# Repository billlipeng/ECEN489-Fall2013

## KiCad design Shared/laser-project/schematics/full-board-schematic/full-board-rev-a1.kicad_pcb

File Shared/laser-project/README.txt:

what implemented:
 Scene set up 
 Planes drawn
 Spheres drawn
 Ambient lighting 
 Diffuse lighting 
 Specular lighting 
 Numbers of Objects, lights, etc. meet requirements

what NOT implement:
 Shadows 
 Reflection (press key '1' to display , press key '2' to restore)

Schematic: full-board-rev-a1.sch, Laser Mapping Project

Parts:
C1, C2, C3, C4, C5, C6, C7, C8, C9, C10, C11, C12, C13: SMCAP; SM1210
CON1: ENCODER-10MIL-HEADER; encoder-10mil-header
CON2: JTAG-10MIL-HDR; JTAG-10mil-hdr
LD1: OPV332; LED-5MM
R1, R2, R3, R4, R5, R6, R7, R8, R9, R10, R11, R12, R13: SMRES; SM1210
T1, T2: BSS138; SOT23
T3: OP598C; LED-5MM
U1: TEENSYPP2
U2, U5: MCP1825; SOT-223-5pin
U3: DS1077; SO8N
U4: AD8302
U6: 6DOF; PIN_ARRAY-6X1
U7: TI-OPA2356

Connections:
/ad8302_inpa: C3.2, U4.2 (INPA)
/ad8302_inpb: C1.2, U4.6 (INPB)
/ad8302_mag: U1.40 (PF0), U4.12 (MSET), U4.13 (VMAG)
/ad8302_ofsa: C4.2, U4.3 (OFSA)
/ad8302_ofsb: C2.2, U4.5 (OFSB)
/ad8302_phs: U1.39 (PF1), U4.9 (VPHS), U4.10 (PSET)
/ad8302_vpos: C9.2, R11.1, U4.4 (VPOS)
/ad8302_vref: U1.41 (AREF), U4.11 (VREF)
/encoder-interface-0: CON1.3, U1.53 (PE4)
/encoder-interface-1: CON1.4, U1.54 (PE5)
/encoder-interface-2: CON1.5, U1.43 (PE6)
/encoder-interface-3: CON1.6, U1.44 (PE7)
/jtag_tck: CON2.1, U1.36 (PF4)
/jtag_tdi: CON2.4, U1.33 (PF7)
/jtag_tdo: CON2.3, U1.34 (PF6)
/jtag_tms: CON2.2, U1.35 (PF5)
/laser_drive_sig: R7.2, U7.1, U7.2
/mod_sig_1: C3.1, R5.2, U3.1 (OUT1), U7.3
/osc_ctrl0: U1.13 (PC0), U3.5 (CTRL0)
/osc_ctrl1: U1.14 (PC1), U3.6 (CTRL1)
/regulator_3.3V: C7.2, CON1.2, R1.2, R4.2, R9.2, T1.1 (G), T2.1 (G), U2.4 (VOUT), U6.6 (3.3V)
/regulator_5V: C5.2, C8.2, C13.2, CON1.1, R3.2, R6.2, R11.2, R12.2, T3.1 (C), U1.21 (VCC), U3.3 (VCC), U5.4 (VOUT), U7.8
/return_sig: C1.1, R2.2, R8.2, T3.2 (E)
/teensy_5V: C6.2, C10.2, U1.52 (VCC), U2.1 (SHDN), U2.2 (VIN), U5.1 (SHDN), U5.2 (VIN)
/twi_scl_3.3V: R1.1, T1.2 (S), U6.3 (SCL)
/twi_scl_5V: R3.1, T1.3 (D), U1.3 (PD0), U3.8 (SCL)
/twi_sda_3.3V: R4.1, T2.2 (S), U6.4 (SDA)
/twi_sda_5V: R6.1, T2.3 (D), U1.4 (PD1), U3.7 (SDA)
GND: C2.1, C4.1, C5.1, C6.1, C7.1, C8.1, C9.1, C10.1, C11.1, C12.1, C13.1, CON1.7, LD1.2, R2.1, R5.1, R8.1, R10.1, R13.1, U1.1 (GND), U1.22 (GND), U1.42 (GND), U2.3 (GND), U2.6 (GNDPAD), U3.4 (GND), U4.1 (COMM), U4.7 (COMM), U5.3 (GND), U5.6 (GNDPAD), U6.5 (GND), U7.4
unnamed: LD1.1, R7.1
unnamed: C12.2, U4.14 (MFLT)
unnamed: C11.2, U4.8 (PFLT)
unnamed: R12.1, R13.2, U5.5 (ADJ)
unnamed: R9.1, R10.2, U2.5 (ADJ)

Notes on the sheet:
C1,C2 May be left open.

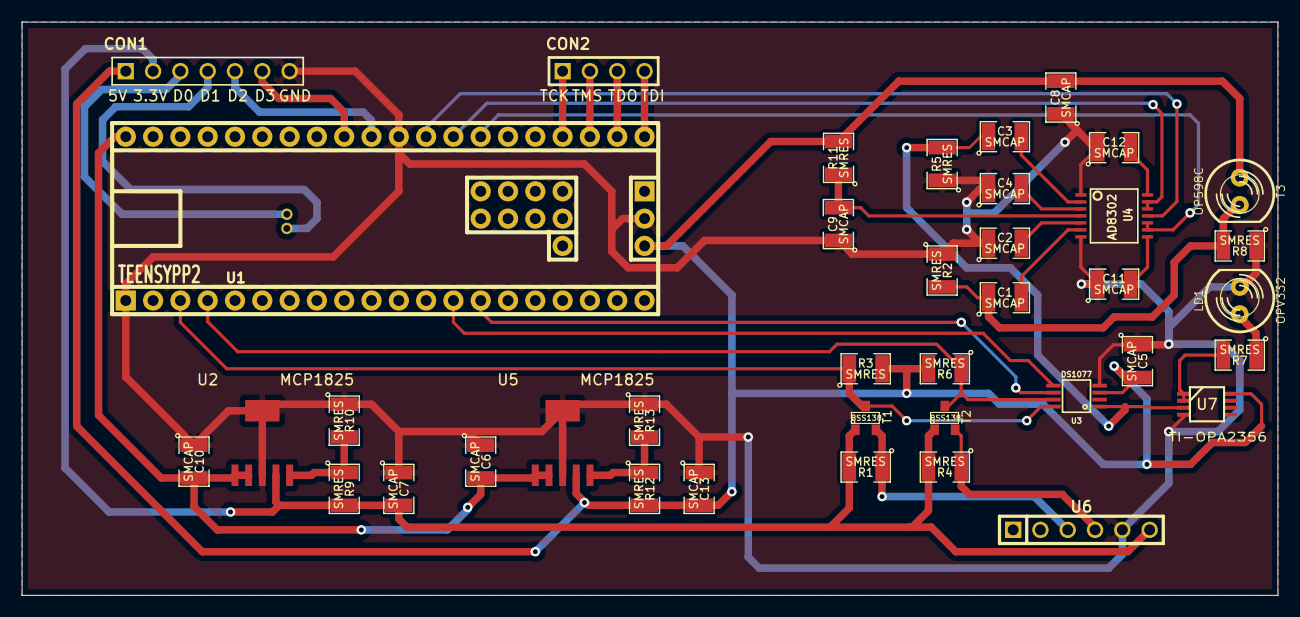
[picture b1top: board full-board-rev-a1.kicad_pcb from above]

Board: 2 copper layers, 116.8 x 53.3 mm, 39 parts (0 on the bottom side), 34 nets.

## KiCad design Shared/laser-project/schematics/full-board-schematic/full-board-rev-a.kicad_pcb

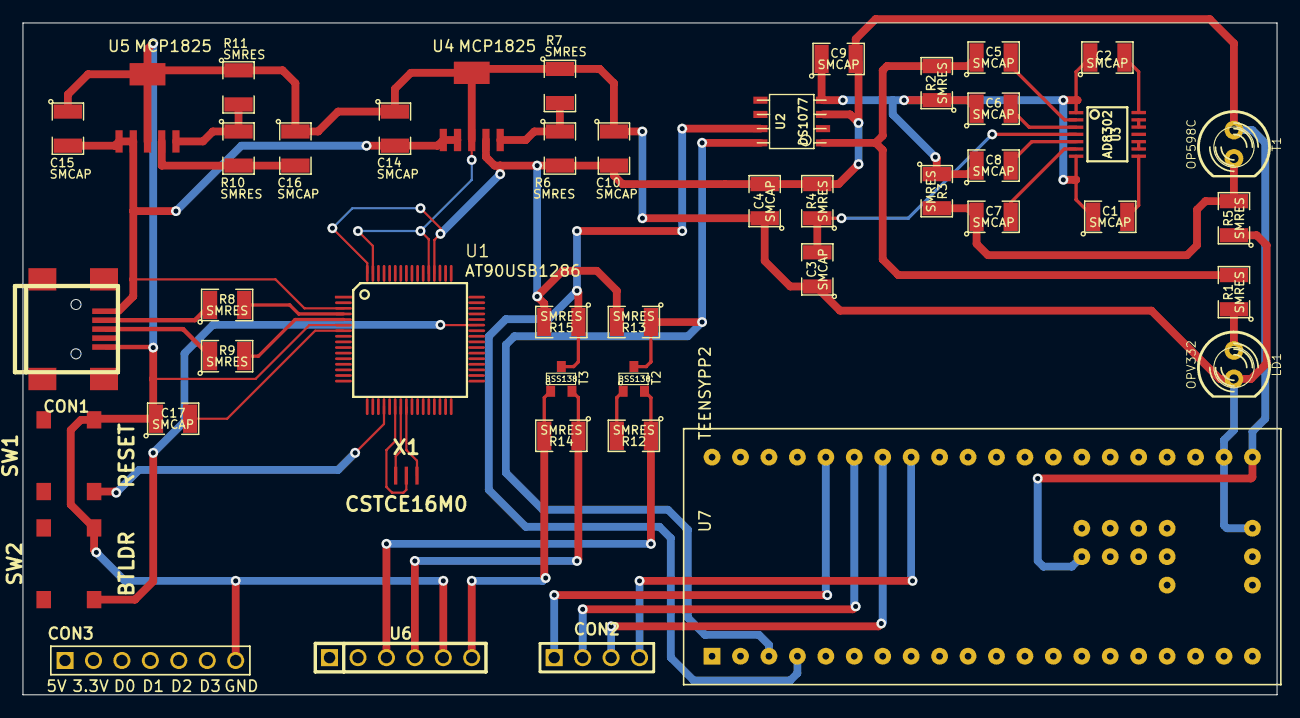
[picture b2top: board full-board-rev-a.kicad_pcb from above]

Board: 2 copper layers, 112.0 x 60.0 mm, 46 parts (0 on the bottom side), 42 nets.

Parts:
C1, C2, C3, C4, C5, C6, C7, C8, C9, C10, C14, C15, C16, C17: SMCAP; SM1210
CON1: USB-MINI-B; usb-mini-b
CON2: JTAG-10MIL-HDR; JTAG-10mil-hdr
CON3: ENCODER-10MIL-HEADER; encoder-10mil-header
LD1: OPV332; LED-5MM
R1, R2, R3, R4, R5, R6, R7, R8, R9, R10, R11, R12, R13, R14, R15: SMRES; SM1210
SW1: RESET; SW
SW2: BTLDR; SW
T1: OP598C; LED-5MM
T2, T3: BSS138; SOT23
U1: AT90USB1286; TQFP_64
U2: DS1077; so-8
U3: AD8302; TSSOP14
U4, U5: MCP1825; SOT-223-5pin
U6: 6DOF; PIN_ARRAY-6X1
U7: TEENSYPP2; Teensy++2.0
X1: CSTCE16M0; 16MHzRES

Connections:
/ad8302_inpa: C5.2, U3.2
/ad8302_inpb: C7.2, U3.6
/ad8302_mag: U1.61, U3.12, U3.13, U7.40
/ad8302_ofsa: C6.2, U3.3
/ad8302_ofsb: C8.2, U3.5
/ad8302_phs: U1.60, U3.9, U3.10, U7.39
/ad8302_vpos: C3.2, R4.1, U3.4
/ad8302_vref: U1.62, U3.11, U7.41
/encoder-interface-0: CON3.3, U1.18
/encoder-interface-1: CON3.4, U1.19
/encoder-interface-2: CON3.5, U1.1, U7.43
/encoder-interface-3: CON3.6, U1.2, U7.44
/hwb_sig: SW2.2, U1.43
/jtag_tck: CON2.1, U1.57, U7.36
/jtag_tdi: CON2.4, U1.54, U7.33
/jtag_tdo: CON2.3, U1.55, U7.34
/jtag_tms: CON2.2, U1.56, U7.35
/mod_sig_1: C5.1, R1.2, R2.2, U2.1
/osc_ctrl0: U1.35, U2.5, U7.13
/osc_ctrl1: U1.36, U2.6, U7.14
/regulator_3.3V: C16.2, CON3.2, R10.2, R12.2, R14.2, T2.1, T3.1, U5.4, U6.6
/regulator_5V: C4.2, C9.2, C10.2, CON3.1, R4.2, R6.2, R13.2, R15.2, T1.1, U1.21, U1.52, U1.64, U2.3, U4.4, U7.21, U7.52
/reset_sig: SW1.2, U1.20
/return_sig: C7.1, R3.2, R5.2, T1.2
/twi_scl_3.3V: R12.1, T2.2, U6.3
/twi_scl_5V: R13.1, T2.3, U1.25, U2.8, U7.3
/twi_sda_3.3V: R14.1, T3.2, U6.4
/twi_sda_5V: R15.1, T3.3, U1.26, U2.7, U7.4
/usb_5V: C14.2, C15.2, CON1.1, U1.3, U1.8, U4.1, U4.2, U5.1, U5.2
/usb_d+: R9.2, U1.5
/usb_d-: R8.2, U1.4
/xtal1_sig: U1.24, X1.3
/xtal2_sig: U1.23, X1.1
GND: C1.1, C2.1, C3.1, C4.1, C6.1, C8.1, C9.1, C10.1, C14.1, C15.1, C16.1, C17.1, CON1.5, CON3.7, LD1.2, R2.1, R3.1, R5.1, R7.1, R11.1, SW1.1, SW2.1, U1.6, U1.22, U1.53, U1.63, U2.4, U3.1, U3.7, U4.3, U4.6, U5.3, U5.6, U6.5, U7.1, U7.22, U7.42, X1.2
unnamed: CON1.3, R9.1
unnamed: CON1.2, R8.1
unnamed: C17.2, U1.7
unnamed: R6.1, R7.2, U4.5
unnamed: R10.1, R11.2, U5.5
unnamed: C1.2, U3.8
unnamed: C2.2, U3.14
unnamed: LD1.1, R1.1

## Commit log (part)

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2013-09-18 Share project "Assignment6" into "https://lemur.tamu.edu/svn/ECEN489-Fall2013"
2013-09-18 Removed some crap that TortoiseSVN added in.
2013-09-18 Share project "Code6-a" into "https://lemur.tamu.edu/svn/ECEN489-Fall2013"
2013-09-18 Share project "Code6-b" into "https://lemur.tamu.edu/svn/ECEN489-Fall2013"
2013-09-22 Our tutorial's documentation
2013-09-23 JsonCpp library
2013-09-23 Tutorial Paper
2013-09-23 Not needed. Replacing with different directory.
2013-09-23 Updating with newer verison.
2013-09-23 Newer version than before.
2013-09-23 Another newer verison to come.
2013-09-23 Another newer version.
2013-09-26 Share project "Cpp_to_PostgreSQL" into "https://lemur.tamu.edu/svn/ECEN489-Fall2013"
2013-09-27 photodiode and thermistor sketches
2013-09-27 forgot the thermistor code
2013-09-28 code tweaks
2013-10-04 Added the motor teams Monday memo.
2013-10-08 Added a small example program that uses libpqxx to print a table.
    It connects to a fixed host, and prints all rows from the
    temp_readings table.
2013-10-10 Control Code
2013-10-11 Control main CPP function code
2013-10-12 Share project "Light_Team_Mini_Project" into "https://lemur.tamu.edu/svn/ECEN489-Fall2013"
2013-10-13 Control Side CPP File
2013-10-13 Fixes on the control-side demo program.
2013-10-13 Final working input side cpp code
2013-10-13 Database connection is working.
2013-10-14 Share project "Mini Project" into "https://lemur.tamu.edu/svn/ECEN489-Fall2013/Shared/motor-project/Input%20Side"
2013-10-14 Share project "Mini Project Control" into "https://lemur.tamu.edu/svn/ECEN489-Fall2013/Shared/motor-project/Input%20Side"
2013-10-23 Added a placeholder file.
2013-10-23 Moved the placeholder to the right place.
2013-10-23 Etc.
2013-10-25 Added the datasheets for the components we're using.
2013-10-25 Move of the phototransistor datasheet.
2013-10-25 Removed improperly named file.
2013-10-25 Renamed datasheets for consistency.
2013-10-25 Removed unnecessary stuff from the visualization program.
2013-10-27 Added progress report.
2013-10-28 Initial work on the integrated schematic.
    Also, found and commited the teensy++ 2.0 schematic, which shows the
    support circuitry needed from the at90usb1286.
2013-10-28 Working on the unified schematic for the laser rangefinder.
    The support circuitry for the at90usb1286 is being drawn from the
    Teensy++2.0 released schematic. Notable points are the direct usb
    connection, the external ceramic 16MHz oscillator, and the external
    reset and bootloader buttons.
    According to the 1286 documentation, the chip ships with a USB DFU
    class bootloader enabled by default. Pulling the HWB pin low during a
2013-10-28 Added USB connector and oscillator.
    Need to check which package of mcp1825 we have tomorrow; that will
    affect the schematic and footprint I put in.
2013-10-28 Finished the progress report for week 1.
    Yeah, it was supposed to be done last Friday. Includes a block
    diagram of the project dataflow, and has been updated with the
    weekends progress.
2013-10-29 PoseTrans.cpp - Contains the main() function for what I am doing. The json directory contains files for the jsoncpp library.
2013-10-30 Updated PoseTrans.cpp to read and parse JSON data from an input file to simulate serial reading. Also added was creating matrices otu of JSON data from an input file, performing matrix multiplication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
2013-10-30 Removed unnecessary input file PoseTransInput. It is generated by PoseTrans.cpp
2013-10-30 Share project "Copy of Mini Project" into "https://lemur.tamu.edu/svn/ECEN489-Fall2013/Shared/motor-project/Input%20Side"
2013-10-30 Share project "AccelPos" into "https://lemur.tamu.edu/svn/ECEN489-Fall2013"
2013-10-30 Added storing product matrices in vectors and minor updates.
2013-10-30 Fixed some silly errors.
2013-10-31 Added: -Laser Module -Phototransistor -Phase Comparator -Oscillator -supporting circuitry -wiring
2013-11-01 Teensy PCB Footprint
2013-11-01 Split lib_489.lib out into separate component libraries.
    Specifically, ad8302.lib/dcm and ds1077.lib/dcm.
2013-11-01 Nearing final version of schematic.
    Subunits have been broken out and connected with labels. and many
    parts have been redrawn. We should no longer be using any standard
    library parts except for the ground symbol.
    Still need to add the IMU components, their 3.3V regulator, and the
    NMOS 5V-3.3V I2C bridge.
    After that, we should just need to lock down some component values,
2013-11-01 Resized the schematic page to US Letter, and made it all fit.
2013-11-02 Fixed some regressions that had happened in the libraries.
    I need to be more careful with my commits.
    Added a schematic symbol for the bss138, an n-mosfet that will be used
    for active conversion between the 5V and 3.3V I2C lines.
2013-11-02 Added 5V to 3.3V I2C Converters with BSS138.
2013-11-04 Added alternate schematic. Only difference is replacing the microcontroller schematic with a teensy++2.0 block. To be determined which is necessary. Need to create header connections for Teensy and s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
2013-11-04 Added PCB footprint for 5 pin SMD MCP1825 package
2013-11-05 -Added IMU to schematic. -assigned footprints to all components -ready to layout PCB (will begin 11/5)
2013-11-05 Preliminary PCB layout complete. Needs routing. Doug will be working on this tonight 5:55pm 11/5/2013
2013-11-06 Removed a few autosave files that had been commited.
2013-11-06 PCB Layout (needs to be routed)
2013-11-07 Added the murata resonator.
    Jeff is making the footpring.
2013-11-07 Finalized schematic.
2013-11-09 Various schematic cleanups.
    Fixed one actual error -- the ad8302 is supposed to be powered by
    ad8302_vpos, not directly by regulator_5V. The only difference is a
    0ohm resistor and some caps.
    Much of the cleanup came about because I was trying to find why the
    rat's nest view for the pcb layout showed the at90usb1286 gnd and vcc
    pins connected. They weren't, actually. Instead, there were many
2013-11-09 Switched usb-mini-b footprint to a locally-defined one.
    The footprint from the KiCad standard library (at least, the one on my
    machine) defined one of the shield pins as usb-d-. This has to be
    wrong, it would cause all kinds of problems.
    The locally-defined one is exactly the same, except that the pin is
    made electrically different from usb-d-.
2013-11-09 Had forgotten to replace some labels.
    While debugging, I had moved some regulator_5V labels to see if they
    were causing a problem. They weren't, but I forgot to move them back.
2013-11-09 Routing progress.
    Have routed the two power supplies and their supporting circuitry.
    Each of these modules only requires the front side of the board.
2013-11-09 Forgot to commit the new usb mod
2013-11-11 Continued routing work.
    I still need to add some encoder interface pins.
2013-11-11 More routing progress.
    Also mounted a teensy++2.0 to the board.
2013-11-11 Routing almost complete.
    It gives me a headache.
2013-11-14 Finished routing.
    We may still need to add a buffer between the oscillator and the laser
    diode. In addition, ground planes need to be added.
2013-11-14 Removed a backup file.
2013-11-14 Forgot to commit the board file.
2013-11-15 Addition of the op-amp, ground planes, and milling finalization.
2013-11-15 Forgot to add the op-amp schematic lib.
    Its layout package is just a standard MSOP-8.
2013-11-18 Qt Master Project as on 11/17/2013 - checked with IMU and Scoring Metric
2013-11-18 Qt Master Project working with IMU and Scoring Metric that includes the angle. Timer is included too!
2013-11-20 Qt Master Project working with 2 IMUs and integrated scoring metric
2013-11-21 Generate points on a unit sphere and translate them (10,10,10)
2013-11-22 A descent final GUI
2013-12-02 Demo simulation of pipe with deformity
2013-12-06 Latex version of final report.
2013-12-06 Final Qt Application for the Hands On Project
